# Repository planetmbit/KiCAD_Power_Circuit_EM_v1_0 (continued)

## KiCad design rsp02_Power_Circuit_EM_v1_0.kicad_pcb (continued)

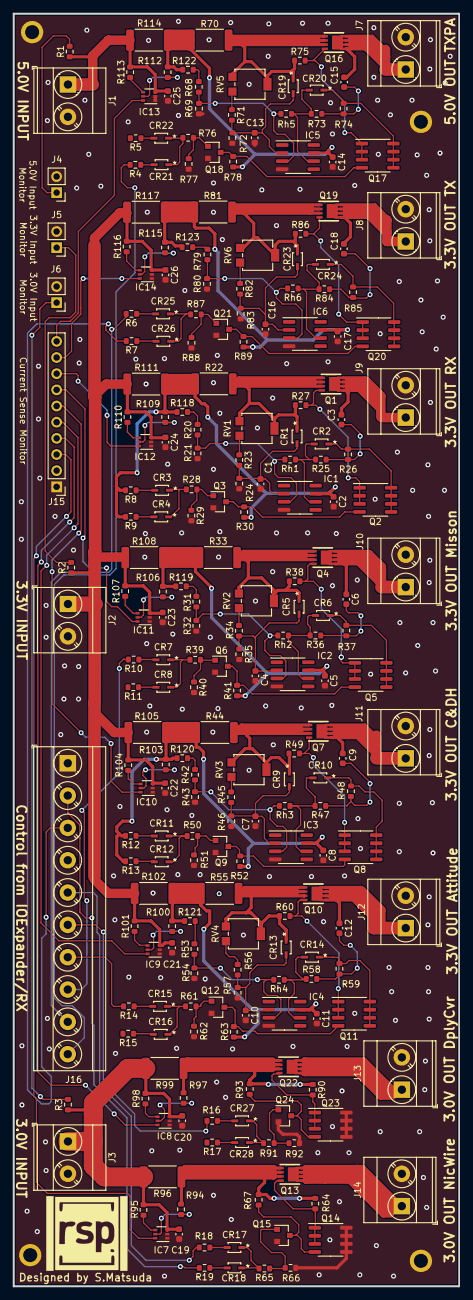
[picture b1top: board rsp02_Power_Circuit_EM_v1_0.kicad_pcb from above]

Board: 2 copper layers, 70.0 x 200.0 mm, 247 parts (0 on the bottom side), 151 nets.

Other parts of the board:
REF1, REF2, REF3, REF4: MountingHole_2.2mm_M2_ISO7380_Pad

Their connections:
GNDA: REF1.1, REF2.1, REF3.1, REF4.1; also elsewhere on the board

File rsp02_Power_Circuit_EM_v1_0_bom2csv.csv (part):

Reference, Value, Footprint, Datasheet, Description, Manufacturer_Name, Manufacturer_Part_Number, RS Part Number, Supplier_Name, ambient temperature range high, ambient temperature range low, automotive, automotive grade, category, collector base voltage, collector emitter saturation voltage, collector emitter voltage, device class L1, device class L2, device class L3, digikey description, digikey part number, emitter base voltage, footprint url, hFE max, hFE min, hFE testIC, hFE testVce, height, ipc land pattern name, lead free, library id, manufacturer, max collector current, max junction temp, mouser description, mouser part number, number of NPN, number of elements, package, power dissipation, rohs, rthja max, temperature range high, unity gain freq, Height, RS Price/Stock
"R8","0","Resistor_SMD:R_0603_1608Metric","~"
"R9","0","Resistor_SMD:R_0603_1608Metric","~"
"R12","0","Resistor_SMD:R_0603_1608Metric","~"
"R13","0","Resistor_SMD:R_0603_1608Metric","~"
"R7","0","Resistor_SMD:R_0603_1608Metric","~"
"R19","0","Resistor_SMD:R_0603_1608Metric","~"
"R18","0","Resistor_SMD:R_0603_1608Metric","~"
"R16","0","Resistor_SMD:R_0603_1608Metric","~"
"R14","0","Resistor_SMD:R_0603_1608Metric","~"
"R10","0","Resistor_SMD:R_0603_1608Metric","~"
"R6","0","Resistor_SMD:R_0603_1608Metric","~"
"R4","0","Resistor_SMD:R_0603_1608Metric","~"
"R5","0","Resistor_SMD:R_0603_1608Metric","~"
"R11","0","Resistor_SMD:R_0603_1608Metric","~"
"R15","0","Resistor_SMD:R_0603_1608Metric","~"
"R17","0","Resistor_SMD:R_0603_1608Metric","~"
"R1","0","Resistor_SMD:R_0603_1608Metric","~"
"R2","0","Resistor_SMD:R_0603_1608Metric","~"
"R3","0","Resistor_SMD:R_0603_1608Metric","~"
"J1","Conn_01x02","TerminalBlock_Phoenix:TerminalBlock_Phoenix_MKDS-3-2-5.08_1x02_P5.08mm_Horizontal","~"
"J2","Conn_01x02","TerminalBlock_Phoenix:TerminalBlock_Phoenix_MKDS-3-2-5.08_1x02_P5.08mm_Horizontal","~"
"J3","Conn_01x02","TerminalBlock_Phoenix:TerminalBlock_Phoenix_MKDS-3-2-5.08_1x02_P5.08mm_Horizontal","~"
"J7","Conn_01x02","TerminalBlock_Phoenix:TerminalBlock_Phoenix_MKDS-3-2-5.08_1x02_P5.08mm_Horizontal","~"
"J15","Conn_01x10","Connector_PinHeader_2.54mm:PinHeader_1x10_P2.54mm_Vertical","~"
"J16","Conn_01x10","TerminalBlock_Phoenix:TerminalBlock_Phoenix_MKDS-3-10-5.08_1x10_P5.08mm_Horizontal","~"
"J4","Conn_01x02","Connector_PinHeader_2.54mm:PinHeader_1x02_P2.54mm_Vertical","~"
"J5","Conn_01x02","Connector_PinHeader_2.54mm:PinHeader_1x02_P2.54mm_Vertical","~"
"J6","Conn_01x02","Connector_PinHeader_2.54mm:PinHeader_1x02_P2.54mm_Vertical","~"
"J8","Conn_01x02","TerminalBlock_Phoenix:TerminalBlock_Phoenix_MKDS-3-2-5.08_1x02_P5.08mm_Horizontal","~"
"J9","Conn_01x02","TerminalBlock_Phoenix:TerminalBlock_Phoenix_MKDS-3-2-5.08_1x02_P5.08mm_Horizontal","~"
"J10","Conn_01x02","TerminalBlock_Phoenix:TerminalBlock_Phoenix_MKDS-3-2-5.08_1x02_P5.08mm_Horizontal","~"
"J11","Conn_01x02","TerminalBlock_Phoenix:TerminalBlock_Phoenix_MKDS-3-2-5.08_1x02_P5.08mm_Horizontal","~"
"J12","Conn_01x02","TerminalBlock_Phoenix:TerminalBlock_Phoenix_MKDS-3-2-5.08_1x02_P5.08mm_Horizontal","~"
"J13","Conn_01x02","TerminalBlock_Phoenix:TerminalBlock_Phoenix_MKDS-3-2-5.08_1x02_P5.08mm_Horizontal","~"
"J14","Conn_01x02","TerminalBlock_Phoenix:TerminalBlock_Phoenix_MKDS-3-2-5.08_1x02_P5.08mm_Horizontal","~"
"R24","1000k","Resistor_SMD:R_0603_1608Metric","~"
"C2","0.1u","Capacitor_SMD:C_0603_1608Metric","~"
"R22","0.05","Resistor_SMD:R_2512_6332Metric","~"
"R26","1k","Resistor_SMD:R_0603_1608Metric","~"
"Rh1","100k","Resistor_SMD:R_0603_1608Metric","~"
"C3","0.1u","Capacitor_SMD:C_0603_1608Metric","~"
"R25","10k","Resistor_SMD:R_0603_1608Metric","~"
"R21","100k","Resistor_SMD:R_0603_1608Metric","~"
"C1","0.1u","Capacitor_SMD:C_0603_1608Metric","~"
"Q1","SISS23DN-T1-GE3","mypartsLib:POWERPAK-1212-8","http://www.vishay.com/docs/62852/siss23dn.pdf","Vishay SISS23DN-T1-GE3 P-channel MOSFET Transistor, 27 A, -20 V, 8-Pin PowerPAK 1212","Vishay","SISS23DN-T1-GE3","8141314","RS","","","","","","","","","","","","","","","","","","","","","","","","","","","","","","","","","","","","","",""
"R27","100k","Resistor_SMD:R_0603_1608Metric","~"
"R30","100k","Resistor_SMD:R_0603_1608Metric","~"
"R29","10k","Resistor_SMD:R_0603_1608Metric","~"
"RV1","200k","Potentiometer_SMD:Potentiometer_Bourns_3314G_Vertical","~"
"Q3","BC848B","Package_TO_SOT_SMD:SOT-23","https://assets.nexperia.com/documents/data-sheet/BC848_SER.pdf","","","","","","+150°C","-65°C","Yes","Grade 0","Trans","30V","200mV","30V","Discrete Semiconductors","Transistors","BJTs","TRANS NPN 30V 0.1A SOT23","1727-4241-1-ND","5V","https://assets.nexperia.com/documents/outline-drawing/SOT23.pdf","450","200","2mA","5V","1.1mm","SOT95P230X100-3","Yes","85bbc30039169e11","Nexperia","100mA","+150°C","BC848 Series 30 V 100 mA SMT NPN General Purpose Transistor - SOT-23","771-BC848B215","1","1","SOT23","250mW","Yes","500K/W","+150°C","100MHz","",""
"CR2","1SS352_H3FT","mypartsLib:1SS352_H3FT","https://toshiba.semicon-storage.com/info/docget.jsp?did=3327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"
"CR1","1SS352_H3FT","mypartsLib:1SS352_H3FT","https://toshiba.semicon-storage.com/info/docget.jsp?did=3327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"
"Q2","IRF7404","Package_SO:SOIC-8_3.9x4.9mm_P1.27mm","http://www.infineon.com/dgdl/irf7404.pdf?fileId=5546d4625336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"
"CR4","1SS352_H3FT","mypartsLib:1SS352_H3FT","https://toshiba.semicon-storage.com/info/docget.jsp?did=3327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"
"CR3","1SS352_H3FT","mypartsLib:1SS352_H3FT","https://toshiba.semicon-storage.com/info/docget.jsp?did=3327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"
"R28","10k","Resistor_SMD:R_0603_1608Metric","~"
"IC1","OP191GSZ_v2","Package_SO:SOIC-8_3.9x4.9mm_P1.27mm","http://uk.rs-online.com/web/p/products/0427284P","Analog Devices OP191GSZ Op Amp, 3MHz Rail-Rail, 3  9 V, 8-Pin SOIC","Analog Devices","OP191GSZ","0427284P","","","","","","","","","","","","","","","","","","","","","","","","","","","","","","","","","","","","","","1.75","http://uk.rs-online.com/web/p/products/0427284P"
"R20","5k","Resistor_SMD:R_0603_1608Metric","~"
"R23","50k","Resistor_SMD:R_0603_1608Metric","~"
"R118","1k","Resistor_SMD:R_0603_1608Metric","~"
"R35","1000k","Resistor_SMD:R_0603_1608Metric","~"
"C5","0.1u","Capacitor_SMD:C_0603_1608Metric","~"
"R33","0.05","Resistor_SMD:R_2512_6332Metric","~"
"R37","1k","Resistor_SMD:R_0603_1608Metric","~"
"Rh2","100k","Resistor_SMD:R_0603_1608Metric","~"
"C6","0.1u","Capacitor_SMD:C_0603_1608Metric","~"
"R36","10k","Resistor_SMD:R_0603_1608Metric","~"
"R32","100k","Resistor_SMD:R_0603_1608Metric","~"
"C4","0.1u","Capacitor_SMD:C_0603_1608Metric","~"
"Q4","SISS23DN-T1-GE3","mypartsLib:POWERPAK-1212-8","http://www.vishay.com/docs/62852/siss23dn.pdf","Vishay SISS23DN-T1-GE3 P-channel MOSFET Transistor, 27 A, -20 V, 8-Pin PowerPAK 1212","Vishay","SISS23DN-T1-GE3","8141314","RS","","","","","","","","","","","","","","","","","","","","","","","","","","","","","","","","","","","","","",""
"R38","100k","Resistor_SMD:R_0603_1608Metric","~"
"R41","100k","Resistor_SMD:R_0603_1608Metric","~"
"R40","10k","Resistor_SMD:R_0603_1608Metric","~"
"RV2","200k","Potentiometer_SMD:Potentiometer_Bourns_3314G_Vertical","~"
"Q6","BC848B","Package_TO_SOT_SMD:SOT-23","https://assets.nexperia.com/documents/data-sheet/BC848_SER.pdf","","","","","","+150°C","-65°C","Yes","Grade 0","Trans","30V","200mV","30V","Discrete Semiconductors","Transistors","BJTs","TRANS NPN 30V 0.1A SOT23","1727-4241-1-ND","5V","https://assets.nexperia.com/documents/outline-drawing/SOT23.pdf","450","200","2mA","5V","1.1mm","SOT95P230X100-3","Yes","85bbc30039169e11","Nexperia","100mA","+150°C","BC848 Series 30 V 100 mA SMT NPN General Purpose Transistor - SOT-23","771-BC848B215","1","1","SOT23","250mW","Yes","500K/W","+150°C","100MHz","",""
"CR6","1SS352_H3FT","mypartsLib:1SS352_H3FT","https://toshiba.semicon-storage.com/info/docget.jsp?did=3327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"
"CR5","1SS352_H3FT","mypartsLib:1SS352_H3FT","https://toshiba.semicon-storage.com/info/docget.jsp?did=3327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"
"Q5","IRF7404","Package_SO:SOIC-8_3.9x4.9mm_P1.27mm","http://www.infineon.com/dgdl/irf7404.pdf?fileId=5546d4625336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"
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
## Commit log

2021-02-27 First Commit from S-MacBookPro
2021-02-27 Update from S-MacBookPro 20210227_2338
2021-02-27 Update from S-MacBookPro 20210227_2339
2021-03-07 Update from S-MacBookPro
2021-03-15 Update for S-MacBookPro
